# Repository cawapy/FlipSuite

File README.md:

# FlipSuite

KiCad schematics and PCBs for building flip dot and flip segment display drivers.

## USE AT YOUR OWN RISK

The designs are not yet finalized or not fully tested.

## Status

### Flips5, Flips6, Flips7

PCBs of [Flips5](Flips5), [Flips6](Flips6) and [Flips7](Flips7),
each in Version V1.0, have been manufactured and equiped.

Flips5, Flips6 and Flips7 can be considered working, at least in single display configurations. Successfully tested:

* Flips5 with standard Brose displays on ``BROSE60`` and ``BRDIC1``, connected to Flips6 on ``CNY1``+``CNY2`` and ``CNX1``
    * 28x16 (15 mm dots)
    * 28x19 (10 mm dots)
* Flips5 with extended 28x24 (10 mm dots) Brose display on ``BROSE60``+``BROSE20`` and ``BRDIC1``, connected to Flips6 on ``CNY1``+``CNY2`` and ``CNX1``
    * This display uses the 24 rows 3-26
* Flips5 with Brose display of 5 digits a 5x7 = 25x7 on ``BROSE34`` and ``BRDIC1``, connected to Flips6 on ``CNY1`` and``CNX1``
* Flips7 with Transit Media displays, connected to Flips6 ``CNY1``+``CNY2`` and ``CNX1``
    * 28x13 (15 mm dots)
    * 28x16 (15 mm dots)
    * 14x16 (15 mm dots)
    * 28x16 (10 mm dots)

Tests of multi display configurations with Flips6 are still pending.

### Flips8

[Flips8](Flips8) is work-in-progress.

## PCBs

View PCBs [online](PCBs.md).

## Known Issues V1.0

### Flips5

* ``R1``, ``R2``, ``R3`` and ``C1``, ``C2``, ``C3`` are too close to the DIP40 sockets of ``IC1``, ``IC2``, ``IC3``;
  When using standard DIP40 sockets with rectangular spring contacts,
  the socket frame and a pad of each of the mentioned resistors and capacitors will overlap.
    * Already rearranged the resistors and capacitors in the layout ([db15812: "Place FP2800As' bypass capacitors and EN-pulldowns to fit in Dip40 socket"](https://github.com/cawapy/FlipSuite/commit/db15812063dd6a5a91f173546fd940a55fbdb63b))
    * Options for manufactured boards
        * Use sockets with slimmer frame (e.g. those with round pins); or pin rows, they are also slimmer than the standard socket frames
        * Use little solder for Rs and Cs, decenter Rs and Cs away from socket frame as much as possible
        * Mill small holes into socket to not collide with housings of Rs and Cs
        * Do not equip the Flips5 PCB with those Rs and Cs
            * The enable signals should have pull down resistors, but they can be provided externally; the Flips6 already provides the enable signals *with* pull down resistors
            * The bypass capacitor can be omitted while the circuit will still work (but it *might* create more radio interferences then)
* Cannot use connector socket *with locks* for ``CN3`` due to conflict with ``BRDIC1`` connector

### Flips6

* Legend with pinout table of ``CN1`` has labels for pins 6 and 8 (``CLK`` vs. ``LAT``) swapped
    * Solution: in the layout, already fixed the table ([aecff96: "Fix wrong labels of Flips6 uP connector: LAT \<--\> CLK"](https://github.com/cawapy/FlipSuite/commit/aecff968aa479d9d29c823dc3a2e2e32617ff91e))

### Flips7

* The jumper ``JP1`` allowing to switch between 28 and 14 column display panel is not required.
  It turned out that both display types do *not* differ regarding pins of columns 4 (and 27).
  The 14 column panel can be used like the 28 column panel.
    * The jumper can be set or even soldered for the 28 column configuration.
    * Jumper to be removed in next version.

## Description

Here is some [technical description](Description.md).

## Flips Systems

* Brose
    * Matrix
        * Minimal:    [..-14 Rows (60P-Connector)](documentation/flips5-13rows.pdf)
        * Typical:    [15-20 Rows (60P-Connector; +**CNY2**)](documentation/flips5-19rows.pdf)
        * Extra:      [21-28 Rows (60P+**20P**-Connectors; +**CNY2**)](documentation/flips5-22rows.pdf)
        * Multi:      [Multiple Display Panels (+**CNX2**, ...)](documentation/flips5-19rows-x3.pdf)
    * Characters
        * [5 Positions a 5x7 Dots (34P-Connector)](documentation/flips5-07rows.pdf)
* Transit Media
    * Small:   [Display with ..-14 Rows](documentation/flips6-1flips7-minimal.pdf)
    * Typical: [Display with 14-16 Rows](documentation/flips6-1flips7.pdf)
    * Multi:   [Multiple Display Panels](documentation/flips6-3flips7.pdf)

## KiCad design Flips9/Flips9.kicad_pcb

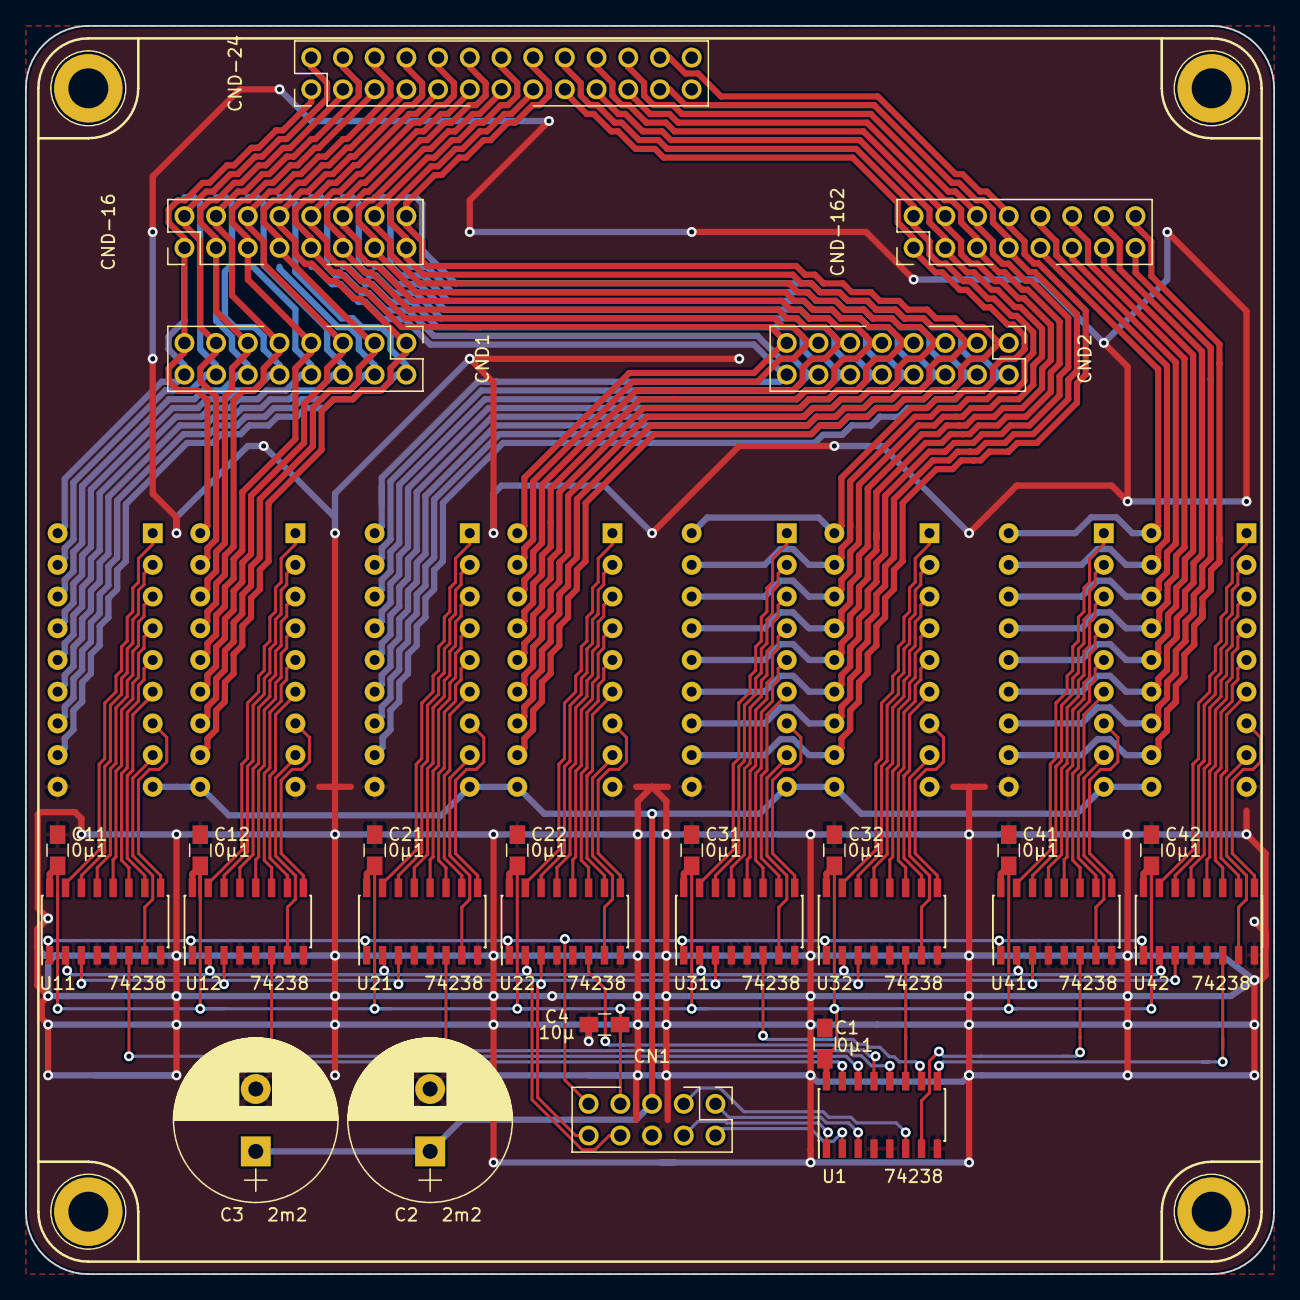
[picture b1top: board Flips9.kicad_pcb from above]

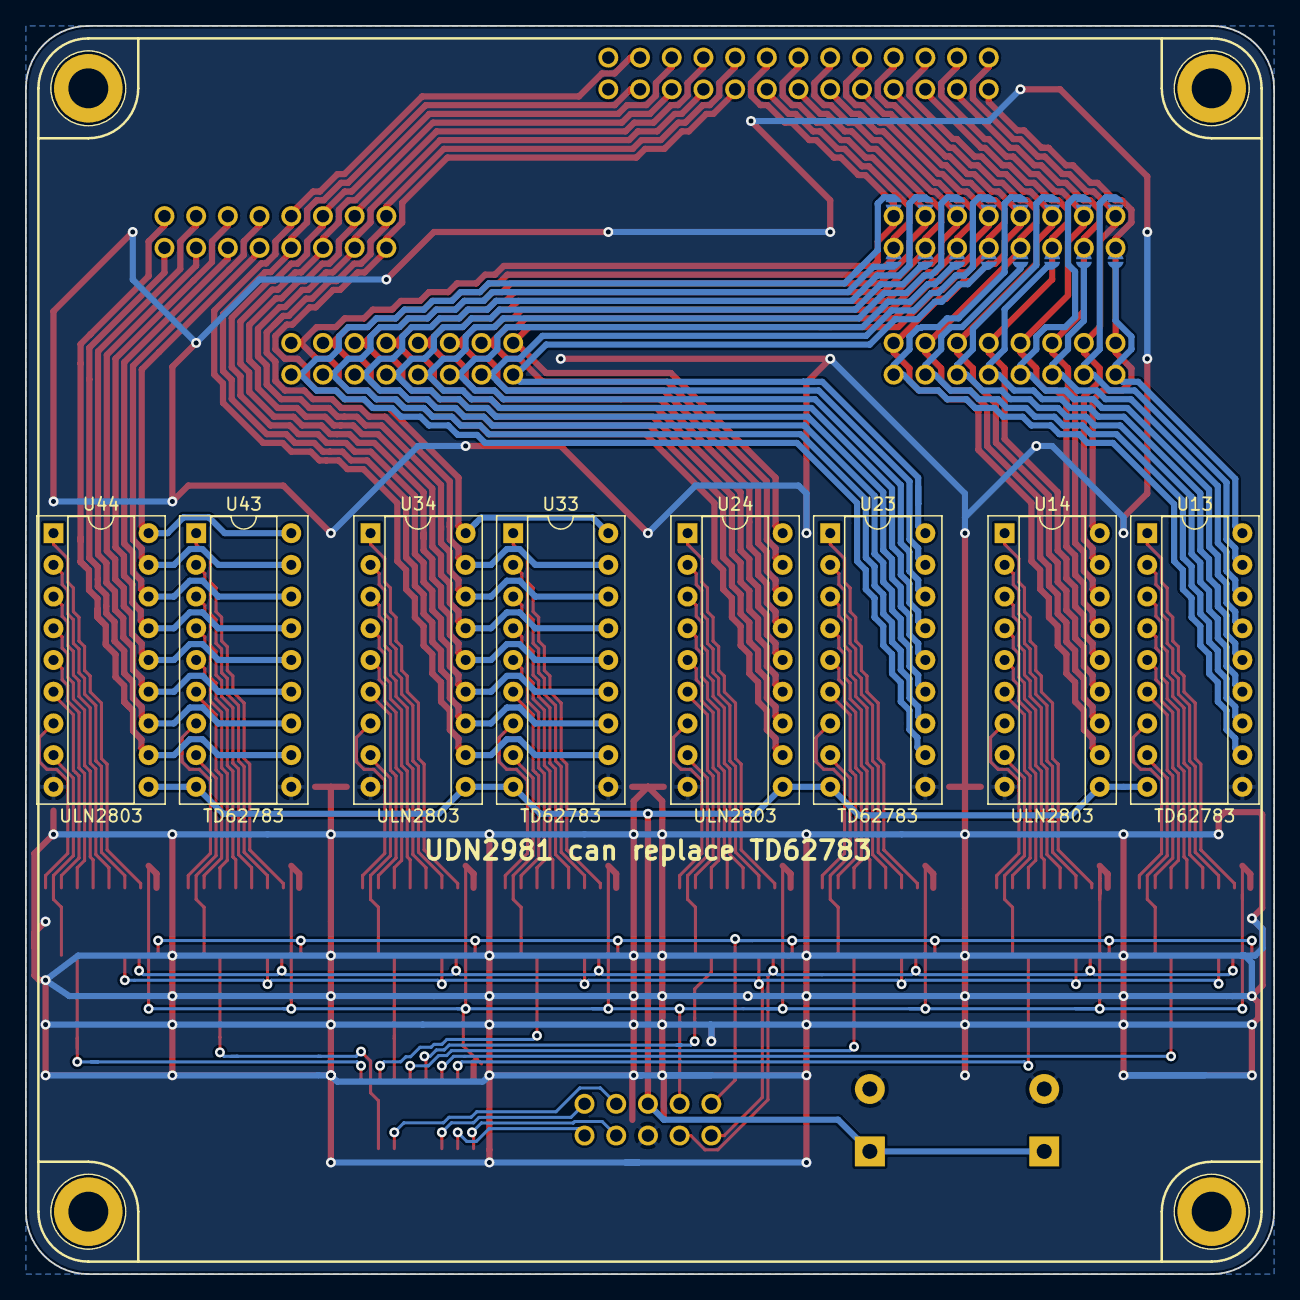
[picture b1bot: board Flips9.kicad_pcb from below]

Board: 2 copper layers, 100.0 x 100.0 mm, 55 parts (24 on the bottom side), 130 nets.

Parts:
C1, C11, C12, C21, C22, C31, C32, C41, C42: 0μ1; C_0805_HandSoldering
C2, C3: 2m2; CP_Radial_D13.0mm_P5.00mm
C4: 10µ; C_0805_HandSoldering
CN1: UFP2810; Pin_Header_Angle_Shrouded_2x05_Pitch2.54mm_ConvNumbering
CND1, CND2: Conn_02x08_Odd_Even; Pin_Header_Straight_Shrouded_Locks_2x08_Pitch2.54mm_ConvNum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
CND-16, CND-162: Conn_02x08_Odd_Even; Pin_Header_Straight_Shrouded_Locks_2x08_Pitch2.54mm_ConvNum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
CND-24: Conn_02x13_Odd_Even; Pin_Header_Straight_Shrouded_Locks_2x13_Pitch2.54mm_ConvNum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
H101, H102, H103, H104: MountingHole; MountingHole_3.2mm_M3_ISO14580_Pad
JP101, JP102, JP103, JP104, JP105, JP106, JP107, JP108, JP109, JP110, JP111, JP112, JP113, JP114, JP115, JP116: Jumper_NO_Small; SolderJumper1.3mmNoSilk
U1, U11, U12, U21, U22, U31, U32, U41, U42: 74238; SOIC-16_3.9x9.9mm_Pitch1.27mm
U13, U23, U33, U43: TD62783; DIP-18_W7.62mm_Socket
U14, U24, U34, U44: ULN2803; DIP-18_W7.62mm_Socket

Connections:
+24V: C2.1, C3.1, CN1.5, U13.9, U14.10, U23.9, U24.10, U33.9, U34.10, U43.9, U44.10
/SX1: CND1.16, JP101.1, U13.18
/SX2: CND1.14, JP102.1, U13.17
/SX3: CND1.12, JP103.1, U13.16
/SX4: CND1.10, JP104.1, U13.15
/SX5: CND1.8, JP105.1, U13.14
/SX6: CND1.6, JP106.1, U13.13
/SX7: CND1.4, JP107.1, U13.12
/SX8: CND1.2, JP108.1, U13.11
/SX9: CND2.16, JP109.1, U23.18
/SX10: CND2.14, JP110.1, U23.17
/SX11: CND2.12, JP111.1, U23.16
/SX12: CND2.10, JP112.1, U23.15
/SX13: CND2.8, JP113.1, U23.14
/SX14: CND2.6, JP114.1, U23.13
/SX15: CND2.4, JP115.1, U23.12
/SX16: CND2.2, JP116.1, U23.11
/UnitY/A0: CN1.9, U11.1, U12.1, U21.1, U22.1, U31.1, U32.1, U41.1, U42.1
/UnitY/A1: CN1.8, U11.2, U12.2, U21.2, U22.2, U31.2, U32.2, U41.2, U42.2
/UnitY/A2: CN1.10, U11.3, U12.3, U21.3, U22.3, U31.3, U32.3, U41.3, U42.3
/UnitY/B0: CN1.2, U1.2
/UnitY/B1: CN1.1, U1.3
/UnitY/DATA: CN1.4, U1.1
/UnitY/E0H: U1.14, U11.6
/UnitY/E0L: U1.15, U12.6
/UnitY/E1H: U1.12, U21.6
/UnitY/E1L: U1.13, U22.6
/UnitY/E2H: U1.10, U31.6
/UnitY/E2L: U1.11, U32.6
/UnitY/E3H: U1.7, U41.6
/UnitY/E3L: U1.9, U42.6
/UnitY/EN: CN1.3, U1.6
/UnitY/Group0/YH1: U11.14, U13.2
/UnitY/Group0/YH2: U11.13, U13.3
/UnitY/Group0/YH3: U11.12, U13.4
/UnitY/Group0/YH4: U11.11, U13.5
/UnitY/Group0/YH5: U11.10, U13.6
/UnitY/Group0/YH6: U11.9, U13.7
/UnitY/Group0/YH7: U11.7, U13.8
/UnitY/Group0/YL1: U12.14, U14.2
/UnitY/Group0/YL2: U12.13, U14.3
/UnitY/Group0/YL3: U12.12, U14.4
/UnitY/Group0/YL4: U12.11, U14.5
/UnitY/Group0/YL5: U12.10, U14.6
/UnitY/Group0/YL6: U12.9, U14.7
/UnitY/Group0/YL7: U12.7, U14.8
/UnitY/Group1/YH1: U21.14, U23.2
/UnitY/Group1/YH2: U21.13, U23.3
/UnitY/Group1/YH3: U21.12, U23.4
/UnitY/Group1/YH4: U21.11, U23.5
/UnitY/Group1/YH5: U21.10, U23.6
/UnitY/Group1/YH6: U21.9, U23.7
/UnitY/Group1/YH7: U21.7, U23.8
/UnitY/Group1/YL1: U22.14, U24.2
/UnitY/Group1/YL2: U22.13, U24.3
/UnitY/Group1/YL3: U22.12, U24.4
/UnitY/Group1/YL4: U22.11, U24.5
/UnitY/Group1/YL5: U22.10, U24.6
/UnitY/Group1/YL6: U22.9, U24.7
/UnitY/Group1/YL7: U22.7, U24.8
/UnitY/Group2/YH1: U31.14, U33.2
/UnitY/Group2/YH2: U31.13, U33.3
/UnitY/Group2/YH3: U31.12, U33.4
/UnitY/Group2/YH4: U31.11, U33.5
/UnitY/Group2/YH5: U31.10, U33.6
/UnitY/Group2/YH6: U31.9, U33.7
/UnitY/Group2/YH7: U31.7, U33.8
/UnitY/Group2/YL1: U32.14, U34.2
/UnitY/Group2/YL2: U32.13, U34.3
/UnitY/Group2/YL3: U32.12, U34.4
/UnitY/Group2/YL4: U32.11, U34.5
/UnitY/Group2/YL5: U32.10, U34.6
/UnitY/Group2/YL6: U32.9, U34.7
/UnitY/Group2/YL7: U32.7, U34.8
/UnitY/Group3/YH1: U41.14, U43.2
/UnitY/Group3/YH2: U41.13, U43.3
/UnitY/Group3/YH3: U41.12, U43.4
/UnitY/Group3/YH4: U41.11, U43.5
/UnitY/Group3/YH5: U41.10, U43.6
/UnitY/Group3/YH6: U41.9, U43.7
/UnitY/Group3/YH7: U41.7, U43.8
/UnitY/Group3/YL1: U42.14, U44.2
/UnitY/Group3/YL2: U42.13, U44.3
/UnitY/Group3/YL3: U42.12, U44.4
/UnitY/Group3/YL4: U42.11, U44.5
/UnitY/Group3/YL5: U42.10, U44.6
/UnitY/Group3/YL6: U42.9, U44.7
/UnitY/Group3/YL7: U42.7, U44.8
/Y1: CND1.15, CND-16.1, CND-24.1, JP101.2, U14.18
/Y2: CND1.13, CND-16.2, CND-24.2, JP102.2, U14.17
/Y3: CND1.11, CND-16.3, CND-24.3, JP103.2, U14.16
/Y4: CND1.9, CND-16.4, CND-24.4, JP104.2, U14.15
/Y5: CND1.7, CND-16.5, CND-24.5, JP105.2, U14.14
/Y6: CND1.5, CND-16.6, CND-24.6, JP106.2, U14.13
/Y7: CND1.3, CND-16.7, CND-24.7, JP107.2, U14.12
/Y8: CND1.1, CND-16.8, CND-24.8, JP108.2, U14.11
/Y9: CND2.15, CND-16.9, CND-24.9, JP109.2, U24.18
/Y10: CND2.13, CND-16.10, CND-24.10, JP110.2, U24.17
/Y11: CND2.11, CND-16.11, CND-24.11, JP111.2, U24.16
/Y12: CND2.9, CND-16.12, CND-24.12, JP112.2, U24.15
/Y13: CND2.7, CND-16.13, CND-24.13, JP113.2, U24.14
/Y14: CND2.5, CND-16.14, CND-24.14, JP114.2, U24.13
/Y15: CND2.3, CND-16.15, CND-24.15, JP115.2, U24.12
/Y16: CND2.1, CND-16.16, CND-24.16, JP116.2, U24.11
/Y17: CND-24.17, CND-162.1, U33.18, U34.18
/Y18: CND-24.18, CND-162.2, U33.17, U34.17
/Y19: CND-24.19, CND-162.3, U33.16, U34.16
/Y20: CND-24.20, CND-162.4, U33.15, U34.15
/Y21: CND-24.21, CND-162.5, U33.14, U34.14
/Y22: CND-24.22, CND-162.6, U33.13, U34.13
/Y23: CND-24.23, CND-162.7, U33.12, U34.12
/Y24: CND-24.24, CND-162.8, U33.11, U34.11
/Y25: CND-162.9, U43.18, U44.18
/Y26: CND-162.10, U43.17, U44.17
/Y27: CND-162.11, U43.16, U44.16
/Y28: CND-162.12, U43.15, U44.15
/Y29: CND-162.13, U43.14, U44.14
/Y30: CND-162.14, U43.13, U44.13
/Y31: CND-162.15, U43.12, U44.12
/Y32: CND-162.16, U43.11, U44.11
GND: C1.2, C2.2, C3.2, C4.2, C11.2, C12.2, C21.2, C22.2, C31.2, C32.2, C41.2, C42.2, CN1.6, U1.4, U1.5, U1.8, U11.4, U11.5, U11.8, U12.4, U12.5, U12.8, U13.10, U14.9, U21.4, U21.5, U21.8, U22.4, U22.5, U22.8, U23.10, U24.9, U31.4, U31.5, U31.8, U32.4, U32.5, U32.8, U33.10, U34.9, U41.4, U41.5, U41.8, U42.4, U42.5, U42.8, U43.10, U44.9
unnamed: U11.15, U13.1
unnamed: U12.15, U14.1
unnamed: U21.15, U23.1
unnamed: U22.15, U24.1
unnamed: U31.15, U33.1
unnamed: U32.15, U34.1
unnamed: U41.15, U43.1
unnamed: U42.15, U44.1
VCC: C1.1, C4.1, C11.1, C12.1, C21.1, C22.1, C31.1, C32.1, C41.1, C42.1, CN1.7, U1.16, U11.16, U12.16, U21.16, U22.16, U31.16, U32.16, U41.16, U42.16

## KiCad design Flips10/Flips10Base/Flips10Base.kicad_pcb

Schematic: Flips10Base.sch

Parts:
C1: 0μ1; C_0805_HandSoldering
CN0, CN1, CN2, CN3: SR28GR; Socket_Strip_Straight_2x08_Pitch2.54mm
IC1: 74138; SOIC-16_3.9x9.9mm_Pitch1.27mm
S1: FP2800A-Interface; DIP-40_W15.24mm

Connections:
+24V: CN0.16, CN1.16, CN2.16, CN3.16, S1.35
/0A: CN0.15, S1.16
/0B: CN0.13, S1.15
/0C: CN0.11, S1.14
/0D: CN0.9, S1.13
/0E: CN0.7, S1.11
/0F: CN0.5, S1.12
/0G: CN0.3, S1.10
/1A: CN1.15, S1.6
/1B: CN1.13, S1.5
/1C: CN1.11, S1.4
/1D: CN1.9, S1.2
/1E: CN1.7, S1.8
/1F: CN1.5, S1.3
/1G: CN1.3, S1.9
/2A: CN2.15, S1.36
/2B: CN2.13, S1.37
/2C: CN2.11, S1.38
/2D: CN2.9, S1.40
/2E: CN2.7, S1.34
/2F: CN2.5, S1.39
/2G: CN2.3, S1.33
/3A: CN3.15, S1.26
/3B: CN3.13, S1.27
/3C: CN3.11, S1.28
/3D: CN3.9, S1.29
/3E: CN3.7, S1.31
/3F: CN3.5, S1.30
/3G: CN3.3, S1.32
/A0: CN0.10, CN1.10, CN2.10, CN3.10, S1.19
/A1: CN0.8, CN1.8, CN2.8, CN3.8, S1.18
/A2: CN0.6, CN1.6, CN2.6, CN3.6, S1.20
/B0: IC1.1 (A0), S1.21
/B1: IC1.2 (A1), S1.22
/COM: CN1.1, S1.1
/DATA: CN0.4, CN1.4, CN2.4, CN3.4, S1.23
/EN: IC1.6 (G1), S1.24
/~ENGR0: CN0.2, IC1.15 (~Y0)
/~ENGR1: CN1.2, IC1.14 (~Y1)
/~ENGR2: CN2.2, IC1.13 (~Y2)
/~ENGR3: CN3.2, IC1.12 (~Y3)
GND: C1.2, CN0.14, CN1.14, CN2.14, CN3.14, IC1.3 (A2), IC1.4 (~G2A), IC1.5 (~G2B), IC1.8 (GND), S1.7, S1.25
VCC: C1.1, CN0.12, CN1.12, CN2.12, CN3.12, IC1.16 (VCC), S1.17

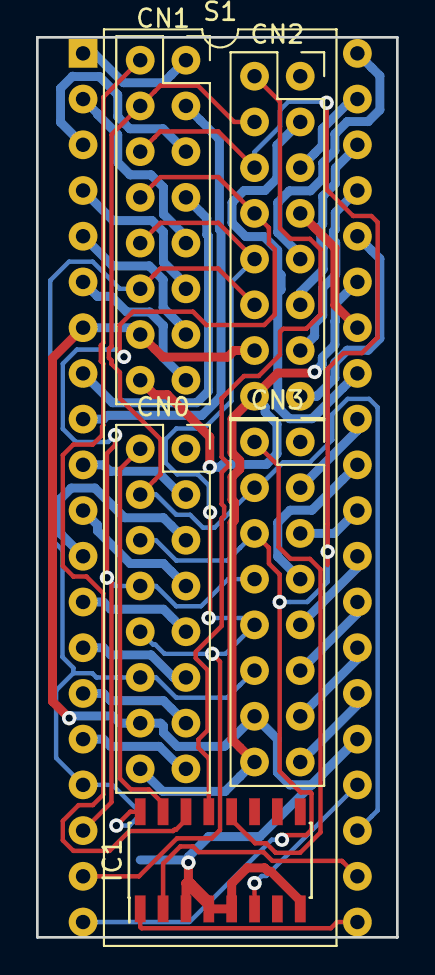
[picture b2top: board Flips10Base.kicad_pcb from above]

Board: 2 copper layers, 20.0 x 50.0 mm, 7 parts (1 on the bottom side), 43 nets.

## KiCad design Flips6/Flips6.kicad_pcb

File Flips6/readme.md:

# Flips6

* View online with [cho45.stfuawsc.com KiCad viewer](https://cho45.stfuawsc.com/kicad-utils/static/viewer.html):
    * [PCB](https://cho45.stfuawsc.com/kicad-utils/static/viewer.html?url=https%3A%2F%2Fgithub.com%2Fcawapy%2FFlipSuite%2Fblob%2Fmaster%2FFlips6%2FFlips6.kicad_pcb)
    * [Schematics](https://cho45.stfuawsc.com/kicad-utils/static/viewer.html?url=https%3A%2F%2Fgithub.com%2Fcawapy%2FFlipSuite%2Fblob%2Fmaster%2FFlips6%2FFlips6.sch)

* 2 independent groups of dependent ports for rows vs. columns
* controlled by 2-3 cascaded 595 shift registers

### Mapping

| # | R0   | R1   | R2?  |
|---|------|------|------|
| 0 | YA.0 | XA.0 | XEN3 |
| 1 | YA.1 | XA.1 | XEN4 |
| 2 | YA.2 | XA.2 | XEN5 |
| 3 | YB.0 | XB.0 | n.c. |
| 4 | YB.1 | XB.1 | n.c. |
| 5 | YDAT | XDAT | n.c. |
| 6 | YEN1 | XEN1 | n.c. |
| 7 | YEN2 | XEN2 | n.c. |

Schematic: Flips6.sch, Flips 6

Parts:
C1, C2, C3: 0µ1; C_0805_HandSoldering
CN1: Conn_02x04_Odd_Even; Pin_Header_Straight_2x04_Pitch2.54mm
CNX1, CNX2, CNX3, CNX4, CNX5, CNX6: UFP2810; Pin_Header_Straight_Shrouded_2x05_Pitch2.54mm
CNY1, CNY2: UFP2810; Pin_Header_Straight_Shrouded_2x05_Pitch2.54mm
IC1, IC2, IC3: 74595; SOIC-16_3.9x9.9mm_Pitch1.27mm
R1, R2, R3, R4, R5, R6, R7, R8, R9, R10: 10k; R_0805_HandSoldering

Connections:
+5V: C1.1, C2.1, C3.1, CN1.1, CNX1.7, CNX2.7, CNX3.7, CNX4.7, CNX5.7, CNX6.7, CNY1.7, CNY2.7, IC1.16 (VCC), IC2.16 (VCC), IC3.16 (VCC), R1.2, R2.2
+12V: CN1.3, CNX1.5, CNX2.5, CNX3.5, CNX4.5, CNX5.5, CNX6.5, CNY1.5, CNY2.5
/DIN: CN1.7, IC1.14 (SER)
/RCLK: CN1.8, IC1.12 (RCLK), IC2.12 (RCLK), IC3.12 (RCLK)
/SRCLK: CN1.6, IC1.11 (SRCLK), IC2.11 (SRCLK), IC3.11 (SRCLK)
/XA.0: CNX1.9, CNX2.9, CNX3.9, CNX4.9, CNX5.9, CNX6.9, IC2.15 (QA)
/XA.1: CNX1.8, CNX2.8, CNX3.8, CNX4.8, CNX5.8, CNX6.8, IC2.1 (QB)
/XA.2: CNX1.10, CNX2.10, CNX3.10, CNX4.10, CNX5.10, CNX6.10, IC2.2 (QC)
/XB.0: CNX1.2, CNX2.2, CNX3.2, CNX4.2, CNX5.2, CNX6.2, IC2.3 (QD)
/XB.1: CNX1.1, CNX2.1, CNX3.1, CNX4.1, CNX5.1, CNX6.1, IC2.4 (QE)
/XDAT: CNX1.4, CNX2.4, CNX3.4, CNX4.4, CNX5.4, CNX6.4, IC2.5 (QF)
/XEN1: CNX1.3, IC2.6 (QG), R5.2
/XEN2: CNX2.3, IC2.7 (QH), R6.2
/XEN3: CNX3.3, IC3.15 (QA), R7.2
/XEN4: CNX4.3, IC3.1 (QB), R8.2
/XEN5: CNX5.3, IC3.2 (QC), R9.2
/XEN6: CNX6.3, IC3.3 (QD), R10.2
/XEN7: IC3.4 (QE)
/XEN8: IC3.5 (QF)
/YA.0: CNY1.9, CNY2.9, IC1.15 (QA)
/YA.1: CNY1.8, CNY2.8, IC1.1 (QB)
/YA.2: CNY1.10, CNY2.10, IC1.2 (QC)
/YB.0: CNY1.2, CNY2.2, IC1.3 (QD)
/YB.1: CNY1.1, CNY2.1, IC1.4 (QE)
/YDAT: CNY1.4, CNY2.4, IC1.5 (QF)
/YEN1: CNY1.3, IC1.6 (QG), R3.2
/YEN2: CNY2.3, IC1.7 (QH), R4.2
/YEN3: IC3.6 (QG)
/YEN4: IC3.7 (QH)
/~OE: CN1.2, IC1.13 (~OE), IC2.13 (~OE), IC3.13 (~OE), R2.1
/~SRCLR: CN1.4, IC1.10 (~SRCLR), IC2.10 (~SRCLR), IC3.10 (~SRCLR), R1.1
GND: C1.2, C2.2, C3.2, CN1.5, CNX1.6, CNX2.6, CNX3.6, CNX4.6, CNX5.6, CNX6.6, CNY1.6, CNY2.6, IC1.8 (GND), IC2.8 (GND), IC3.8 (GND), R3.1, R4.1, R5.1, R6.1, R7.1, R8.1, R9.1, R10.1
unnamed: IC1.9 (QH'), IC2.14 (SER)
unnamed: IC2.9 (QH'), IC3.14 (SER)

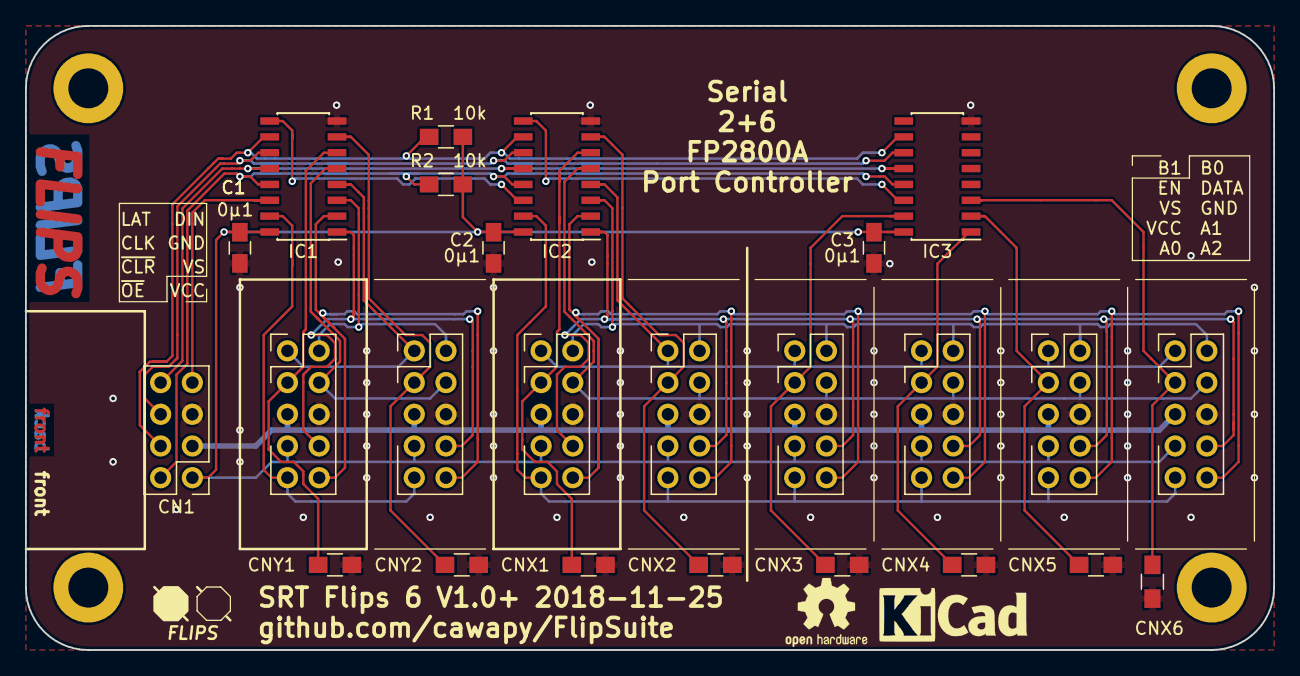
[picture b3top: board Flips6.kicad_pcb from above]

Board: 2 copper layers, 100.0 x 50.0 mm, 25 parts (0 on the bottom side), 30 nets.

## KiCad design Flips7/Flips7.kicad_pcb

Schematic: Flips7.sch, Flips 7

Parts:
BOARD1: Conn_02x30_Top_Bottom; Pin_Header_Straight_Shrouded_2x30_Pitch2.54mm_AltNumbering
C1, C2, C3: 0µ1; C_0805_HandSoldering
CNX1: UFP2810; Pin_Header_Angle_Shrouded_2x05_Pitch2.54mm_ConvNumbering
CNY1, CNY2: UFP2810; Pin_Header_Angle_Shrouded_2x05_Pitch2.54mm_ConvNumbering
IC1, IC2, IC3: FP2800A; DIP-40_W15.24mm_Socket
JP1: Jumper_Cross; Cross_Jumper_2x2_2.54mm
R1, R2, R3: 10k; R_0805_HandSoldering
SHR1, SHR2: Conn_02x17_Odd_Even; Pin_Header_Straight_Shrouded_2x17_Pitch2.54mm_ConvNumbering

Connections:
/HV: CNX1.5, CNY1.5, CNY2.5, IC1.35, IC2.35, IC3.35
/RY01: BOARD1.18, IC1.36, SHR1.22, SHR2.22
/RY02: BOARD1.13, IC1.37, SHR1.24, SHR2.24
/RY03: BOARD1.9, IC1.38, SHR1.26, SHR2.26
/RY04: BOARD1.21, IC1.40, SHR1.30, SHR2.30
/RY05: BOARD1.24, IC1.34, SHR1.18, SHR2.18
/RY06: BOARD1.6, IC1.39, SHR1.28, SHR2.28
/RY07: BOARD1.3, IC1.33, SHR1.16, SHR2.16
/RY08: BOARD1.27, IC1.26, SHR1.2, SHR2.2
/RY09: BOARD1.30, IC1.27, SHR1.4, SHR2.4
/RY10: BOARD1.45, IC1.28, SHR1.6, SHR2.6
/RY11: BOARD1.58, IC1.29, SHR1.8, SHR2.8
/RY12: BOARD1.32, IC1.31, SHR1.12, SHR2.12
/RY13: BOARD1.37, IC1.30, SHR1.10, SHR2.10
/RY14: BOARD1.14, IC1.32, SHR1.14, SHR2.14
/RY15: BOARD1.52, IC2.36, SHR1.32, SHR2.32
/RY16: BOARD1.51, IC2.37, SHR1.34, SHR2.34
/VCC: C1.2, C2.1, C3.1, CNX1.7, CNY1.7, CNY2.7, IC1.17, IC2.17, IC3.17
/X01: BOARD1.35, IC3.16
/X02: BOARD1.34, IC3.15
/X03: BOARD1.33, IC3.14
/X04: IC3.13, JP1.4
/X04_NC: BOARD1.44, JP1.2
/X05: BOARD1.42, IC3.11
/X06: BOARD1.41, IC3.12
/X07: BOARD1.40, IC3.10
/X08: BOARD1.39, IC3.6
/X09: BOARD1.36, IC3.5
/X10: BOARD1.12, IC3.4
/X11: BOARD1.1, IC3.2
/X12: BOARD1.4, IC3.8
/X13: BOARD1.7, IC3.3
/X14: BOARD1.10, IC3.9
/X15: BOARD1.16, IC3.36
/X16: BOARD1.19, IC3.37
/X17: BOARD1.22, IC3.38
/X18: BOARD1.25, IC3.40
/X19: BOARD1.28, IC3.34
/X20: BOARD1.59, IC3.39
/X21: BOARD1.57, IC3.33
/X22: BOARD1.50, IC3.26
/X23: BOARD1.48, IC3.27
/X24: BOARD1.47, IC3.28
/X25: BOARD1.46, IC3.29
/X26: BOARD1.56, IC3.31
/X27: IC3.30, JP1.1
/X27_X04: BOARD1.55, JP1.3
/X28: BOARD1.54, IC3.32
/X.A0: CNX1.9, IC3.19
/X.A1: CNX1.8, IC3.18
/X.A2: CNX1.10, IC3.20
/X.B0: CNX1.2, IC3.21
/X.B1: CNX1.1, IC3.22
/X.EN: CNX1.3, IC3.24, R3.1
/X.POL: CNX1.4, IC3.23
/Y1.A0: CNY1.9, IC1.19
/Y1.A1: CNY1.8, IC1.18
/Y1.A2: CNY1.10, IC1.20
/Y1.B0: CNY1.2, IC1.21
/Y1.B1: CNY1.1, IC1.22
/Y1.EN: CNY1.3, IC1.24, R1.1
/Y1.POL: CNY1.4, IC1.23
/Y2.A0: CNY2.9, IC2.19
/Y2.A1: CNY2.8, IC2.18
/Y2.A2: CNY2.10, IC2.20
/Y2.B0: CNY2.2, IC2.21
/Y2.B1: CNY2.1, IC2.22
/Y2.EN: CNY2.3, IC2.24, R2.1
/Y2.POL: CNY2.4, IC2.23
/~SY01: BOARD1.17, IC1.16, SHR1.1, SHR2.1
/~SY02: BOARD1.11, IC1.15, SHR1.3, SHR2.3
/~SY03: BOARD1.8, IC1.14, SHR1.5, SHR2.5
/~SY04: BOARD1.20, IC1.13, SHR1.7, SHR2.7
/~SY05: BOARD1.23, IC1.11, SHR1.11, SHR2.11
/~SY06: BOARD1.5, IC1.12, SHR1.9, SHR2.9
/~SY07: BOARD1.2, IC1.10, SHR1.13, SHR2.13
/~SY08: BOARD1.26, IC1.6, SHR1.21, SHR2.21
/~SY09: BOARD1.29, IC1.5, SHR1.23, SHR2.23
/~SY10: BOARD1.43, IC1.4, SHR1.25, SHR2.25
/~SY11: BOARD1.60, IC1.2, SHR1.29, SHR2.29
/~SY12: BOARD1.31, IC1.8, SHR1.17, SHR2.17
/~SY13: BOARD1.38, IC1.3, SHR1.27, SHR2.27
/~SY14: BOARD1.15, IC1.9, SHR1.15, SHR2.15
/~SY15: BOARD1.53, IC2.16, SHR1.31, SHR2.31
/~SY16: BOARD1.49, IC2.15, SHR1.33, SHR2.33
GND: C1.1, C2.2, C3.2, CNX1.6, CNY1.6, CNY2.6, IC1.7, IC1.25, IC2.7, IC2.25, IC3.7, IC3.25, R1.2, R2.2, R3.2, SHR1.19, SHR1.20, SHR2.19, SHR2.20

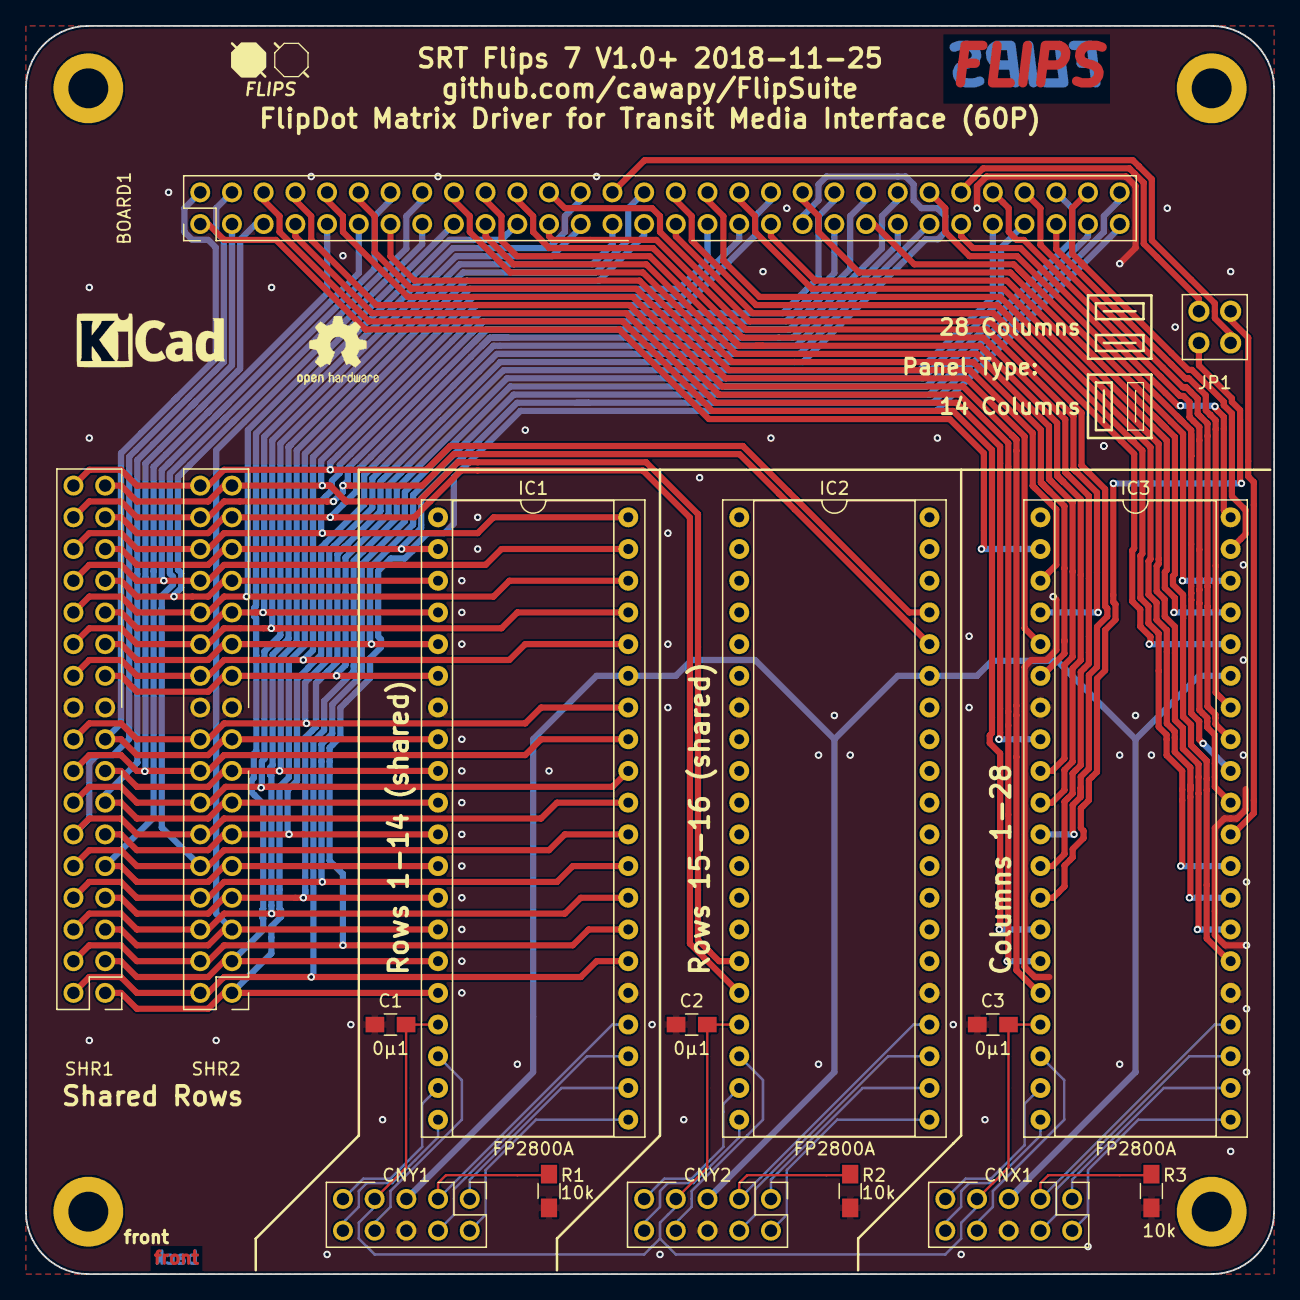
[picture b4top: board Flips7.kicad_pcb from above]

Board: 2 copper layers, 100.0 x 100.0 mm, 16 parts (0 on the bottom side), 86 nets.

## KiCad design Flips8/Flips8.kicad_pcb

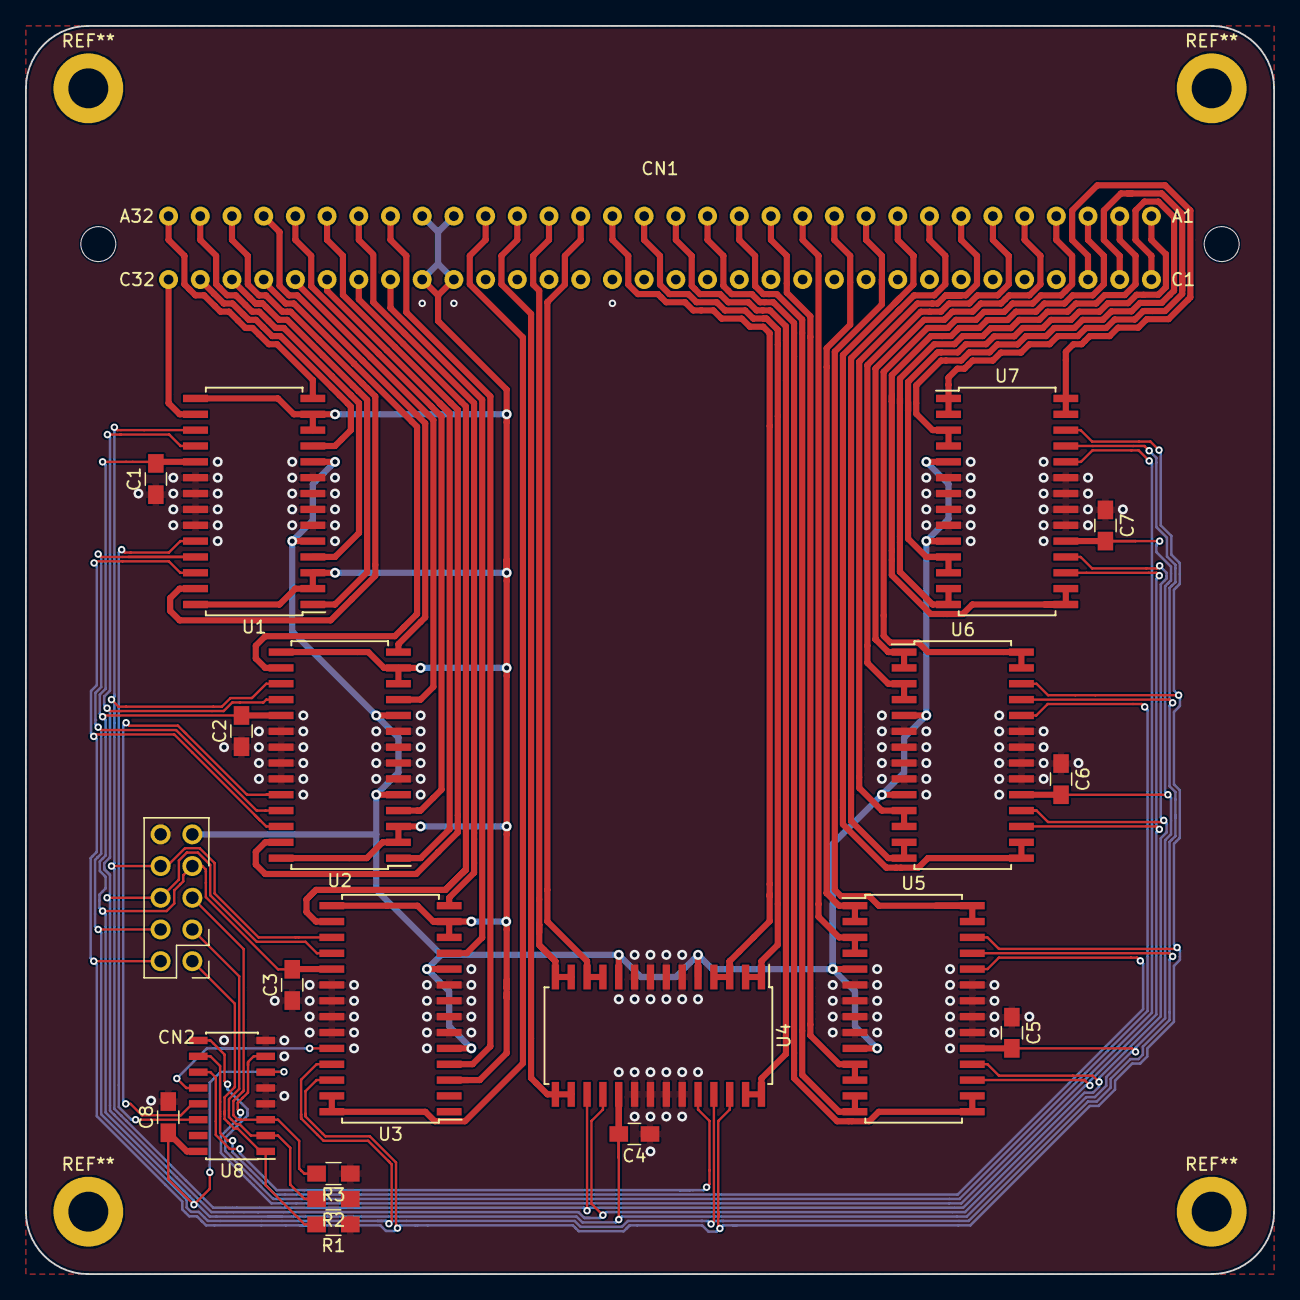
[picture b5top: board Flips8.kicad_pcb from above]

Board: 2 copper layers, 100.0 x 100.0 mm, 21 parts (0 on the bottom side), 59 nets.

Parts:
C1, C2, C3, C4, C5, C6, C7, C8: 0μ1; C_0805_HandSoldering
CN1: Conn_02x32_Row_Letter_First_A_C; Annax-Connector
CN2: Conn_02x05_Odd_Even; Pin_Header_Angle_Shrouded_2x05_Pitch2.54mm_ConvNumbering
R1, R2, R3: 10k; R_0805_HandSoldering
U1, U2, U3, U4, U5, U6, U7: NCV7708; SOIC-28W_7.5x17.9mm_Pitch1.27mm
U8: 74LS138; SOIC-16_3.9x9.9mm_Pitch1.27mm

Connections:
+12V: CN2.9, U1.5, U1.10, U2.5, U2.10, U3.5, U3.10, U4.5, U4.10, U5.5, U5.10, U6.5, U6.10, U7.5, U7.10
/CSA0: CN2.1, R1.2, U8.1
/CSA1: CN2.3, R2.2, U8.2
/CSA2: CN2.5, R3.2, U8.3
/EN: CN2.8, U1.17, U2.17, U3.17, U4.17, U5.17, U6.17, U7.17
/RY: CN1.A23, CN1.A24, CN1.C23, CN1.C24, U1.2, U1.3, U1.12, U1.13, U1.15, U1.28, U2.2, U2.3, U2.12, U2.13, U2.15, U2.28, U3.3, U3.12, U3.13, U3.15
/SCLK: CN2.4, U1.25, U2.25, U3.25, U4.25, U5.25, U6.25, U7.25
/SI: CN2.2, U1.26, U2.26, U3.26, U4.26, U5.26, U6.26, U7.26
/SO: CN2.6, U1.18, U2.18, U3.18, U4.18, U5.18, U6.18, U7.18
/X1: CN1.A22, U3.27, U3.28
/X2: CN1.A21, U4.15, U4.16
/X3: CN1.A20, U4.13, U4.14
/X4: CN1.A19, U4.11, U4.12
/X5: CN1.A18, U4.3, U4.4
/X6: CN1.A17, U4.1, U4.2
/X7: CN1.A16, U4.27, U4.28
/X8: CN1.A15, U5.15, U5.16
/X9: CN1.A14, U5.13, U5.14
/X10: CN1.A13, U5.11, U5.12
/X11: CN1.A12, U5.3, U5.4
/X12: CN1.A11, U5.1, U5.2
/X13: CN1.A10, U5.27, U5.28
/X14: CN1.A9, U6.15, U6.16
/X15: CN1.A8, U6.13, U6.14
/X16: CN1.A7, U6.11, U6.12
/X17: CN1.A6, U6.3, U6.4
/X18: CN1.A5, U6.1, U6.2
/X19: CN1.A4, U6.27, U6.28
/X20: CN1.A3, U7.15, U7.16
/X21: CN1.A2, U7.13, U7.14
/X22: CN1.A1, U7.11, U7.12
/X23: CN1.C1, U7.3, U7.4
/X24: CN1.C2, U7.1, U7.2
/X25: CN1.C3, U7.27, U7.28
/~CS1: U1.24, U8.14
/~CS2: U2.24, U8.13
/~CS3: U3.24, U8.12
/~CS4: U4.24, U8.11
/~CS5: U5.24, U8.10
/~CS6: U6.24, U8.9
/~CS7: U7.24, U8.7
/~SY1: CN1.C32, U1.16
/~SY2: CN1.A32, U1.14
/~SY3: CN1.C31, U1.11
/~SY4: CN1.A31, U1.4
/~SY5: CN1.C30, U1.1
/~SY6: CN1.A30, U1.27
/~SY7: CN1.C29, U2.16
/~SY8: CN1.A29, U2.14
/~SY9: CN1.C28, U2.11
/~SY10: CN1.A28, U2.4
/~SY11: CN1.C27, U2.1
/~SY12: CN1.A27, U2.27
/~SY13: CN1.C26, U3.16
/~SY14: CN1.A26, U3.14
/~SY15: CN1.C25, U3.11
/~SY16: CN1.A25, U3.4
GND: C1.1, C2.1, C3.1, C4.1, C5.1, C6.1, C7.1, C8.2, CN2.10, R1.1, R2.1, R3.1, U1.6, U1.7, U1.8, U1.9, U1.20, U1.21, U1.22, U1.23, U2.6, U2.7, U2.8, U2.9, U2.20, U2.21, U2.22, U2.23, U3.6, U3.7, U3.8, U3.9, U3.20, U3.21, U3.22, U3.23, U4.6, U4.7, U4.8, U4.9, U4.20, U4.21, U4.22, U4.23, U5.6, U5.7, U5.8, U5.9, U5.20, U5.21, U5.22, U5.23, U6.6, U6.7, U6.8, U6.9, U6.20, U6.21, U6.22, U6.23, U7.6, U7.7, U7.8, U7.9, U7.20, U7.21, U7.22, U7.23, U8.4, U8.5, U8.8
VCC: C1.2, C2.2, C3.2, C4.2, C5.2, C6.2, C7.2, C8.1, CN2.7, U1.19, U2.19, U3.19, U4.19, U5.19, U6.19, U7.19, U8.6, U8.16

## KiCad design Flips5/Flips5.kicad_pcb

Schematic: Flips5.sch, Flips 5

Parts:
BRDIC1: Conn_02x17_Odd_Even; Pin_Header_Angle_Shrouded_2x17_Pitch2.54mm_ConvNumbering
BROSE20: Conn_02x10_Odd_Even; Pin_Header_Straight_Shrouded_2x10_Pitch2.54mm_ConvNumbering
BROSE34: Conn_02x17_Odd_Even; Pin_Header_Angle_Shrouded_2x17_Pitch2.54mm_ConvNumbering
BROSE60: Conn_02x30_Odd_Even; Pin_Header_Straight_Shrouded_2x30_Pitch2.54mm_ConvNumbering
C1, C2, C3: 0μ1; C_0805_HandSoldering
CNX1: UFP2810; Pin_Header_Angle_Shrouded_2x05_Pitch2.54mm
CNY1, CNY2: UFP2810; Pin_Header_Angle_Shrouded_2x05_Pitch2.54mm
IC1, IC2, IC3: FP2800A; DIP-40_W15.24mm_Socket
R1, R2, R3: 10k; R_0805_HandSoldering

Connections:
/GND: C1.1, C2.2, C3.2, CNX1.6, CNY1.6, CNY2.6, IC1.7, IC1.25, IC2.7, IC2.25, IC3.7, IC3.25, R1.1, R2.1, R3.1
/HV: CNX1.5, CNY1.5, CNY2.5, IC1.35, IC2.35, IC3.35
/SY1: BROSE34.19, BROSE60.1, IC1.16
/SY2: BROSE34.21, BROSE60.2, IC1.15
/SY3: BROSE34.23, BROSE60.3, IC1.14
/SY4: BROSE34.25, BROSE60.4, IC1.13
/SY5: BROSE34.27, BROSE60.5, IC1.11
/SY6: BROSE34.29, BROSE60.6, IC1.12
/SY7: BROSE34.31, BROSE60.7, IC1.10
/SY8: BROSE60.8, IC1.6
/SY9: BROSE60.9, IC1.5
/SY10: BROSE60.10, IC1.4
/SY11: BROSE60.11, IC1.2
/SY12: BROSE60.12, IC1.8
/SY13: BROSE60.13, IC1.3
/SY14: BROSE60.14, IC1.9
/SY15: BROSE60.15, IC2.16
/SY16: BROSE60.16, IC2.15
/SY17: BROSE60.17, IC2.14
/SY18: BROSE60.18, IC2.13
/SY19: BROSE60.19, IC2.11
/SY20: BROSE60.20, IC2.12
/SY21: BROSE20.1, IC2.10
/SY22: BROSE20.2, IC2.6
/SY23: BROSE20.3, IC2.5
/SY24: BROSE20.4, IC2.4
/SY25: BROSE20.5, IC2.2
/SY26: BROSE20.6, IC2.8
/SY27: BROSE20.7, IC2.3
/SY28: BROSE20.8, IC2.9
/VCC: C1.2, C2.1, C3.1, CNX1.7, CNY1.7, CNY2.7, IC1.17, IC2.17, IC3.17
/X1: BRDIC1.32, IC3.16
/X2: BRDIC1.30, IC3.15
/X3: BRDIC1.28, IC3.14
/X4: BRDIC1.26, IC3.13
/X5: BRDIC1.22, IC3.11
/X6: BRDIC1.24, IC3.12
/X7: BRDIC1.20, IC3.10
/X8: BRDIC1.12, IC3.6
/X9: BRDIC1.10, IC3.5
/X10: BRDIC1.8, IC3.4
/X11: BRDIC1.4, IC3.2
/X12: BRDIC1.16, IC3.8
/X13: BRDIC1.6, IC3.3
/X14: BRDIC1.18, IC3.9
/X15: BRDIC1.9, IC3.36
/X16: BRDIC1.7, IC3.37
/X17: BRDIC1.5, IC3.38
/X18: BRDIC1.1, IC3.40
/X19: BRDIC1.13, IC3.34
/X20: BRDIC1.3, IC3.39
/X21: BRDIC1.15, IC3.33
/X22: BRDIC1.29, IC3.26
/X23: BRDIC1.27, IC3.27
/X24: BRDIC1.25, IC3.28
/X25: BRDIC1.23, IC3.29
/X26: BRDIC1.19, IC3.31
/X27: BRDIC1.21, IC3.30
/X28: BRDIC1.17, IC3.32
/X.A0: CNX1.9, IC3.19
/X.A1: CNX1.8, IC3.18
/X.A2: CNX1.10, IC3.20
/X.B0: CNX1.2, IC3.21
/X.B1: CNX1.1, IC3.22
/X.EN: CNX1.3, IC3.24, R3.2
/X.POL: CNX1.4, IC3.23
/Y1.A0: CNY1.9, IC1.19
/Y1.A1: CNY1.8, IC1.18
/Y1.A2: CNY1.10, IC1.20
/Y1.B0: CNY1.2, IC1.21
/Y1.B1: CNY1.1, IC1.22
/Y1.EN: CNY1.3, IC1.24, R1.2
/Y1.POL: CNY1.4, IC1.23
/Y2.A0: CNY2.9, IC2.19
/Y2.A1: CNY2.8, IC2.18
/Y2.A2: CNY2.10, IC2.20
/Y2.B0: CNY2.2, IC2.21
/Y2.B1: CNY2.1, IC2.22
/Y2.EN: CNY2.3, IC2.24, R2.2
/Y2.POL: CNY2.4, IC2.23
/~RY1: BROSE34.20, BROSE60.21, IC1.36
/~RY2: BROSE34.22, BROSE60.22, IC1.37
/~RY3: BROSE34.24, BROSE60.23, IC1.38
/~RY4: BROSE34.26, BROSE60.24, IC1.40
/~RY5: BROSE34.28, BROSE60.25, IC1.34
/~RY6: BROSE34.30, BROSE60.26, IC1.39
/~RY7: BROSE34.32, BROSE60.27, IC1.33
/~RY8: BROSE60.28, IC1.26
/~RY9: BROSE60.29, IC1.27
/~RY10: BROSE60.30, IC1.28
/~RY11: BROSE60.31, IC1.29
/~RY12: BROSE60.32, IC1.31
/~RY13: BROSE60.33, IC1.30
/~RY14: BROSE60.34, IC1.32
/~RY15: BROSE60.35, IC2.36
/~RY16: BROSE60.36, IC2.37
/~RY17: BROSE60.37, IC2.38
/~RY18: BROSE60.38, IC2.40
/~RY19: BROSE60.39, IC2.34
/~RY20: BROSE60.40, IC2.39
/~RY21: BROSE20.9, IC2.33
/~RY22: BROSE20.10, IC2.26
/~RY23: BROSE20.11, IC2.27
/~RY24: BROSE20.12, IC2.28
/~RY25: BROSE20.13, IC2.29
/~RY26: BROSE20.14, IC2.31
/~RY27: BROSE20.15, IC2.30
/~RY28: BROSE20.16, IC2.32
